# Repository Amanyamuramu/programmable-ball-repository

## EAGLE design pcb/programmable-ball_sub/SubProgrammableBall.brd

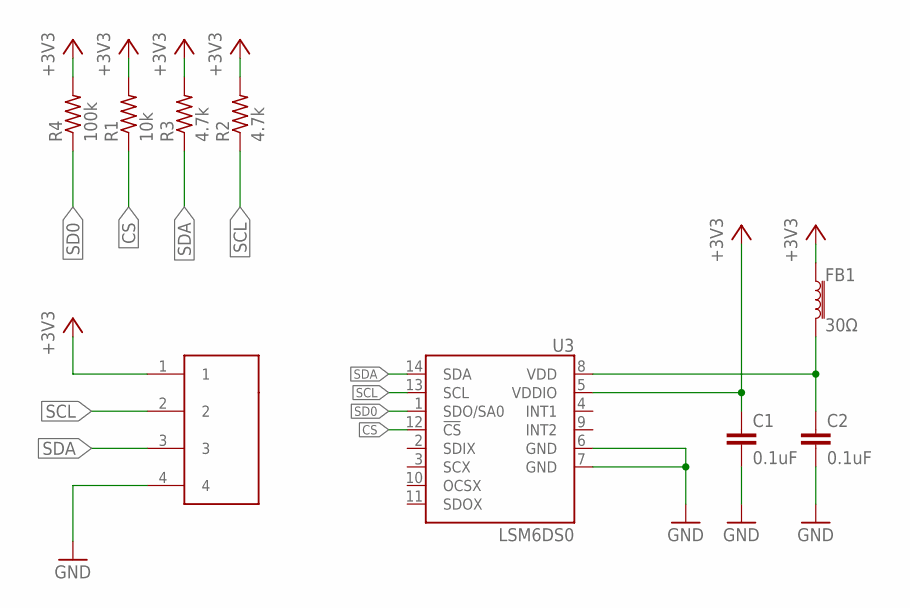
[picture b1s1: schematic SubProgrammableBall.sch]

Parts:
C1, C2: 0.1uF; C0603
CON1: B4B-ZR-SM4-TF; CONN_B4B-ZR-SM4-TF
FB1: 30Ω; 0603
R1: 10k; R0603
R2, R3: 4.7k; R0603
R4: 100k; R0603
U3: LSM6DS0; LGA14L

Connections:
+3V3: C1.1, CON1.1, FB1.1, R1.2, R2.2, R3.2, R4.2, U3.5 (VDDIO)
CS: R1.1, U3.12 (!CS!)
GND: C1.2, C2.2, CON1.4, U3.6 (GND), U3.7 (GND)
unnamed: C2.1, FB1.2, U3.8 (VDD)
SCL: CON1.2, R2.1, U3.13 (SCL)
SD0: R4.1, U3.1 (SDO/SA0)
SDA: CON1.3, R3.1, U3.14 (SDA)

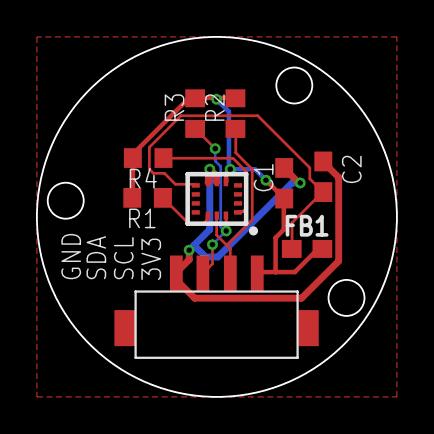
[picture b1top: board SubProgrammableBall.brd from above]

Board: 2 copper layers, 20.0 x 20.0 mm, 9 parts (0 on the bottom side), 7 nets.

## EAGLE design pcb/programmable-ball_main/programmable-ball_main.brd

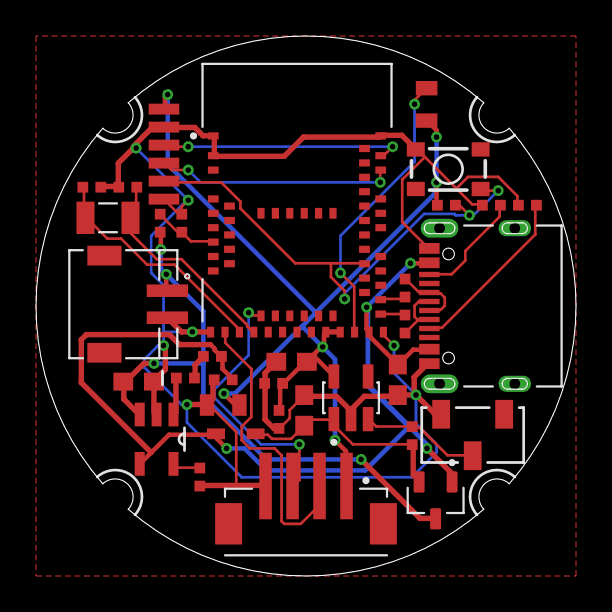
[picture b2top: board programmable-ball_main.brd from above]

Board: 2 copper layers, 30.0 x 30.0 mm, 34 parts (0 on the bottom side), 24 nets.

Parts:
C1, C2: 9.1pF; 0402-TIGHT
C3, C4, C5, C6: 10uF; 0603
C7, C8: 0.1uF; 0402-TIGHT
D1: MBR120LSFT1G; SOD323
D2: RED; LED-0402
DNP: 84981-6RE; 84981-6
J1: 12402012E212A; AMPHENOL_12402012E212A
J3: B4B-ZR-SM4-TFT(LF)(SN); JST_B4B-ZR-SM4-TFT(LF)(SN)
L1: DNP; 0805
L2: 10μH; 0805
P1: S2B-ZR-SM4A-TF; JST_S2B-ZR-SM4A-TF
Q1: DMG2305UX-13; SOT91P240X110-3N
R1, R2: 5.1k; 0402-TIGHT
R3: 47k; 0402-TIGHT
R4, R5, R10, R11: 100k; 0402-TIGHT
R6: 4.7k; 0402-TIGHT
R7: 1k; 0402-TIGHT
R8, R9: 22Ω; 0402-TIGHT
S1: SWITCH-MOMENTARY-SPSTSMD-3; TACTILE_SWITCH_SMD-3
S2: CASA-120TA-PB; CAS-120A
U1: MDBT50Q-1MV2; XCVR_MDBT50Q-1MV2
U2: AP2112K-3.3TRG1; SOT95P285X140-5N
U3: MCP73832T-2ACI/OT; SOT95P270X145-5N
Y1: FC-135_32.7680KA-A0; XTAL_FC-135_32.7680KA-A0

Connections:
3.3V: C5.1, C7.1, C8.1, DNP.1, J3.1, L1.1, L2.1, R3.2, U1.28, U1.30, U2.5
EN: R4.1, S2.2, U2.3
GND: C1.2, C2.2, C3.2, C4.2, C5.2, C6.2, C7.2, C8.2, DNP.2, DNP.6, J1.A1_B12, J1.B1_A12, J3.4, L2.2, P1.2, R1.1, R2.1, R5.1, R6.1, R11.1, S1.1, S2.3, U1.1, U1.2, U1.15, U1.33, U1.55, U2.2, U3.2
I2C_SCL: J3.2, U1.16
I2C_SDA: J3.3, U1.19
unnamed: J1.A5, R1.2
unnamed: J1.B5, R2.2
unnamed: C2.1, U1.18, Y1.2
unnamed: C1.1, U1.17, Y1.1
unnamed: L1.2, U1.31
unnamed: C3.1, D1.1, Q1.2, R4.2, U2.1
unnamed: R6.2, U3.5
unnamed: D2.C, U3.1
unnamed: D2.A, R7.2
unnamed: R8.1, U1.35
unnamed: R9.1, U1.34
RESET: DNP.5, R3.1, S1.4, U1.40
SWDCLK: DNP.3, U1.53
SWDIO: DNP.4, U1.51
USBD+: J1.A6, J1.B6, R8.2
USBD-: J1.A7, J1.B7, R9.2
VBAT: C4.1, P1.1, Q1.3, R10.2, U3.3
VBUS: C6.1, D1.2, J1.A4_B9, J1.B4_A9, Q1.1, R5.2, R7.1, U1.32, U3.4
VDIV: R10.1, R11.2, U1.10

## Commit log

2024-02-23 Added BLE接続用ブラウザ
2024-02-23 Added mp3 free素材
2024-02-23 Added gitignore
2024-02-23 Added FW Connection using BLE
2024-02-23 modify html button appearance
2024-02-23 acc取得してBLEに流す用のFW追加
2024-02-23 加速度センサが動くコード。rmsの計算・シリアルの出力がされる
2024-02-23 動作用に処理修正
2024-02-23 Added acc sensor lib
2024-02-23 RMSの処理を追加
2024-02-23 軽微な修正
2024-02-25 filterモジュールを追加
2024-02-25 ハイパス後の加速度ローデータを用いてRMSに反映するように変更
2024-02-25 ACC's RSM custom #2
2024-02-25 acc,hfp,commit create close #2
2024-03-01 メイン回路のプロジェクト作成
2024-03-01 nRFを基板に搭載し、大きさ見てみた #4
2024-03-01 軽微な修正 #4
2024-03-01 vscode以下を管理対象外に設定
2024-03-02 Added ignore directory(pdf)
2024-03-02 Added Circular Board and TypeC Connector #4
2024-03-02 試し用のガーバーデータ書き出し
2024-03-02 usb typeC周り実装 #4
2024-03-02 Added ignore Eagle's Auto router files
2024-03-02 スイッチを追加 #4
2024-03-03 3.3VのレギュレータとVBATよりVBUSを優先するように修正
2024-03-03 スライドスイッチを追加 #4
2024-03-03 配置を微修正
2024-03-03 主電源スイッチとリポ充放電素子を追加 #4
2024-03-04 リポ充放電機能を搭載 #4
2024-03-05 パターンの位置調整
2024-03-07 コネクタとコンデンサを追加 #4
2024-03-08 基盤外形を変更
2024-03-08 基盤外形追加
2024-03-08 基板v1完成 resolved #4
2024-03-08 v1のガーバーデータ書き出し
2024-03-10 v1の修正
2024-03-10 パターン調整前を最新版に変更
2024-03-10 v2の軽微な修正
2024-03-10 v2ガーバーデータ書き出し
2024-03-13 sub基板のbrd上で部品配置まで。これから配線
2024-03-14 garber data
2024-03-14 brd, schの更新
2024-03-14 ベタ変更
2024-03-18 シルクの削除
2024-03-18 最新版に変更
2024-03-18 最終版(v3)のガーバーデータ書き出し
2024-03-18 サブ基板のガーバーデータ書き出し
2024-03-18 発注用のガーバーデータを専用フォルダに移動
2024-03-28 筐体のためのSTL追加
2024-04-06 加速度センサのfoot print間違い修正
2024-04-06 筐体のstl追加
2024-04-06 Ignore ideaMaker working file
2024-04-06 added first project for programmable ball
2024-04-08 バッテリ残量が表示されるように修正
2024-04-08 added battery appearance in html
2024-05-29 LSM6DSOを使用するために整理
2024-05-29 i2cスキャナーを追加
2024-05-29 不要な処理はコメントアウト
2024-05-29 加速度センサLSM6DSOに対応するように修正
2024-05-29 rmsの値をシリアルにて確認できるように修正
2024-05-29 文章を微修正
2024-05-29 mp3のデータ追加
2024-05-29 mp3データと連続処理の追加
2024-05-29 組み立て完成後のアセンブリファイル追加
2024-05-29 パスを変更
2024-05-29 ランダムのバージョンに戻した
2024-05-29 通信用データ接頭辞に文字記号を追加
2024-05-30 テキストの条件分岐に半角の空白を追加
2024-05-30 ポーリングに変更，不要なシリアル出力を削除
2024-05-30 ポーリング形式に修正，不要なシリアル出力を削除
2024-05-30 ジャイロ描画用のスクリプト作成
2024-06-03 ボール外形用3Dデータ追加
2024-06-03 unity Projectと音声ファイルを無視
2024-07-06 効果音追加
2024-07-06 fw修正
2024-07-06 音声読み込みソース変更
2024-07-06 rmsの閾値強度を変更
2024-07-06 音ファイルを変更
2024-07-06 twitterの着信に変更

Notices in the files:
parts and their libraries:
SparkFun-Resistors: Licensing: Creative Commons ShareAlike 4.0 International - https://creativecommons.org/licenses/by-sa/4.0
